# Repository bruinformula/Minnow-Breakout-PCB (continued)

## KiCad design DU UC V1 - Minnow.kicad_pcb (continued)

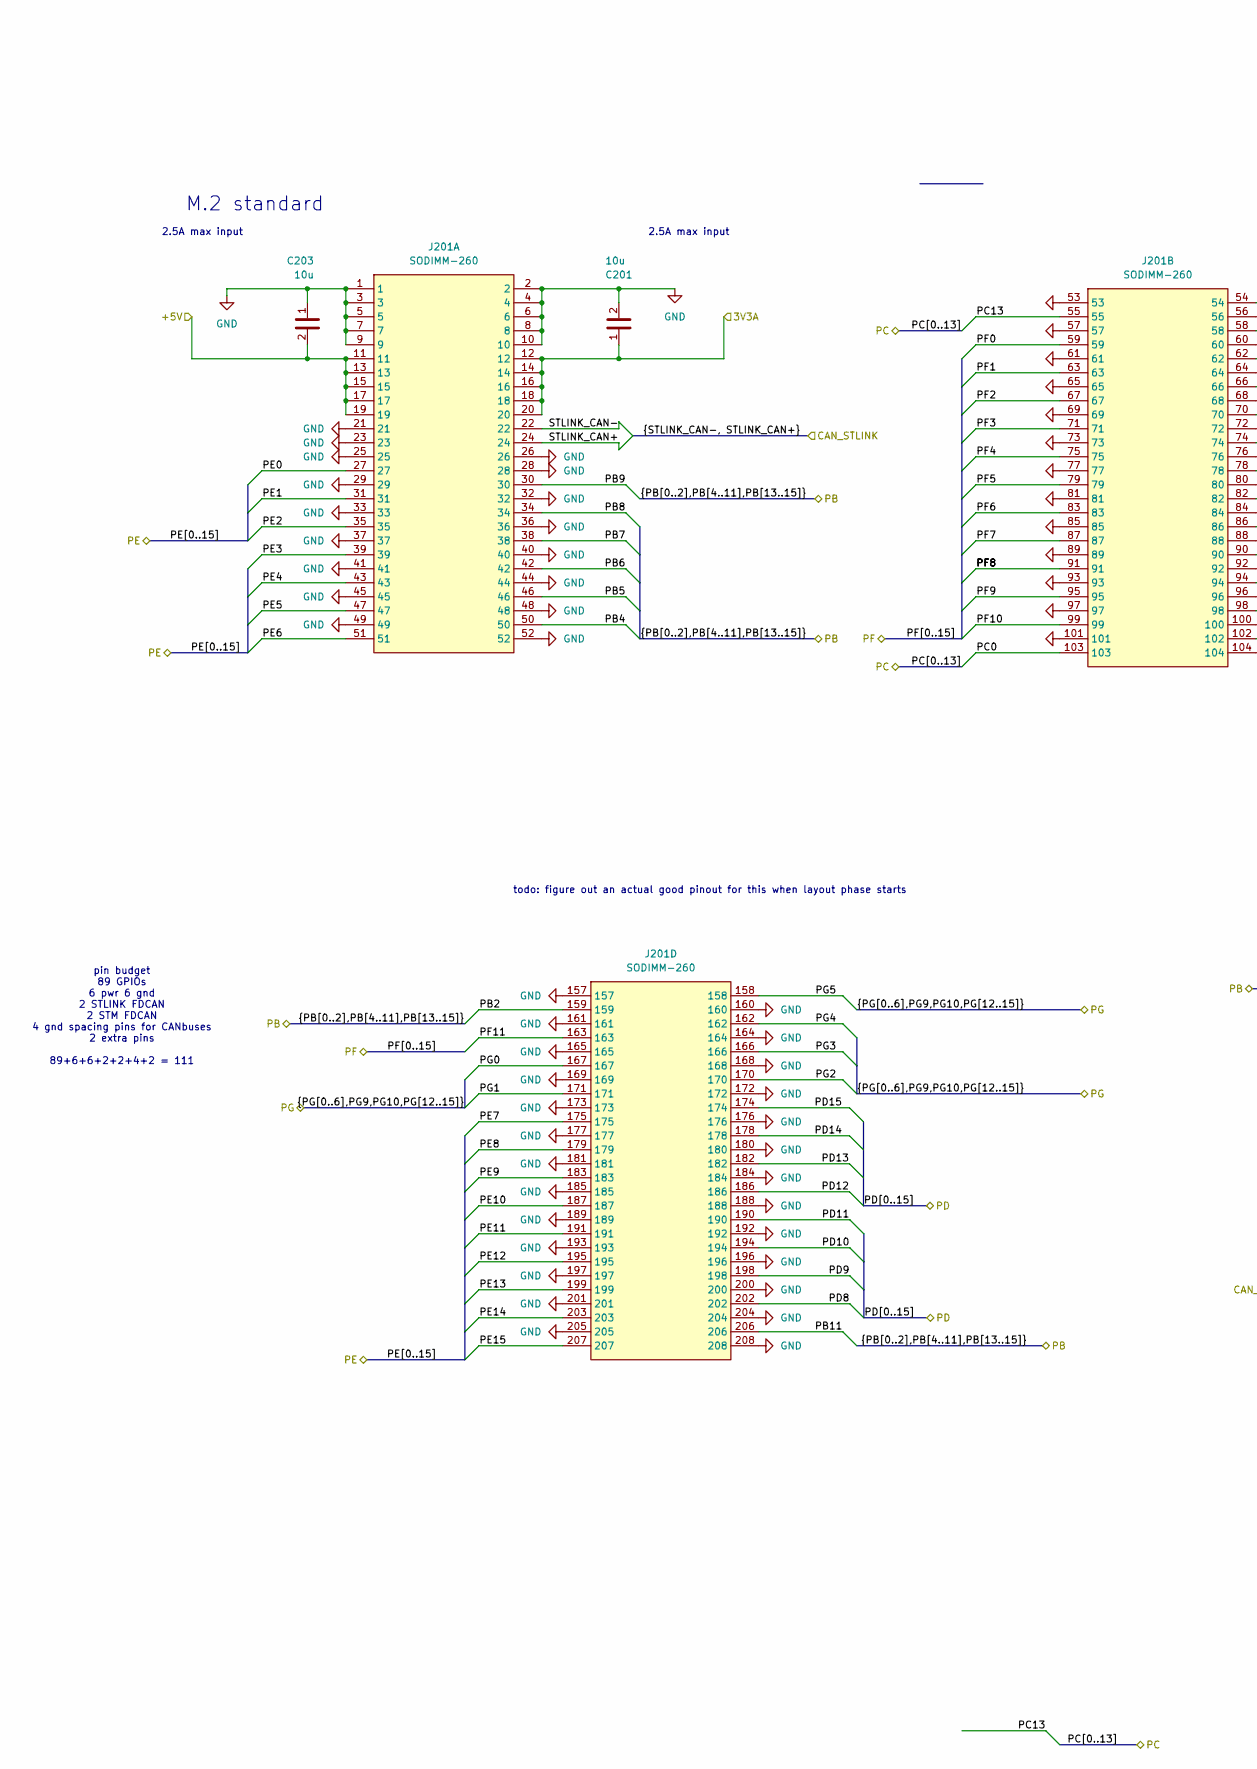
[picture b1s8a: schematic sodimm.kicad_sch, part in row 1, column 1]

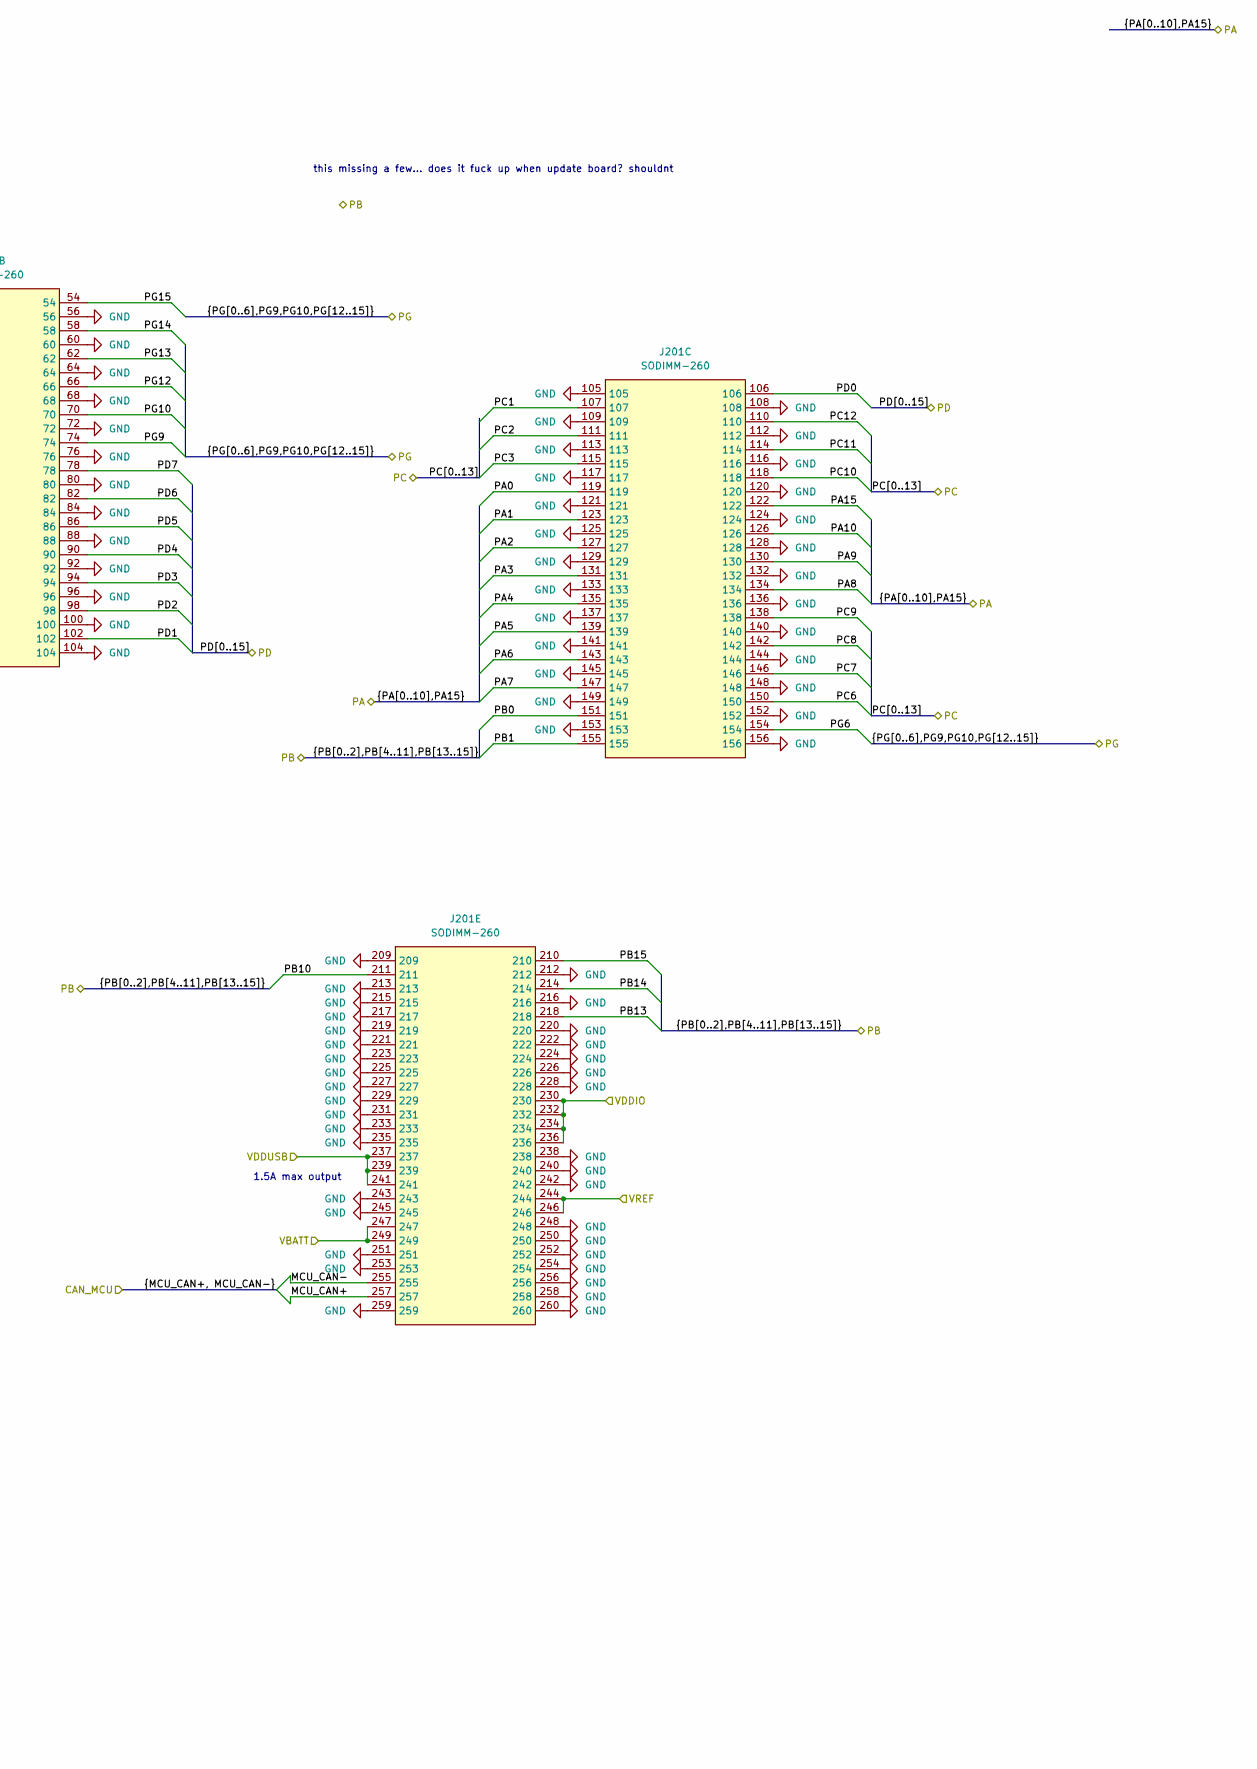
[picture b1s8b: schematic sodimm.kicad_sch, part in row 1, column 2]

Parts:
C201, C203: 10u; C_0603_1608Metric_Pad1.08x0.95mm_HandSolder; Mouser P/N 81-GRM188R61E106MA3D
J201: SODIMM-260; SODIMM-260 DDR4; Manufacturer P/N 2309407-1; Digikey P/N A126758TR-ND

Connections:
/3V3A_RAW: C201.1, J201.12, J201.14, J201.16, J201.18, J201.20; also elsewhere on the board
/5V_RAW: C203.2, J201.11, J201.13, J201.15, J201.17, J201.19; also elsewhere on the board
/SODIMM Connector/MCU_CAN+: J201.257; also elsewhere on the board
/SODIMM Connector/MCU_CAN-: J201.255; also elsewhere on the board
/SODIMM Connector/PA0: J201.119; also elsewhere on the board
/SODIMM Connector/PA1: J201.123; also elsewhere on the board
/SODIMM Connector/PA2: J201.127; also elsewhere on the board
/SODIMM Connector/PA3: J201.131; also elsewhere on the board
/SODIMM Connector/PA4: J201.135; also elsewhere on the board
/SODIMM Connector/PA5: J201.139; also elsewhere on the board
/SODIMM Connector/PA6: J201.143; also elsewhere on the board
/SODIMM Connector/PA7: J201.147; also elsewhere on the board
/SODIMM Connector/PA8: J201.134; also elsewhere on the board
/SODIMM Connector/PA9: J201.130; also elsewhere on the board
/SODIMM Connector/PA10: J201.126; also elsewhere on the board
/SODIMM Connector/PA15: J201.122; also elsewhere on the board
/SODIMM Connector/PB0: J201.151; also elsewhere on the board
/SODIMM Connector/PB1: J201.155; also elsewhere on the board
/SODIMM Connector/PB2: J201.159; also elsewhere on the board
/SODIMM Connector/PB4: J201.50; also elsewhere on the board
/SODIMM Connector/PB5: J201.46; also elsewhere on the board
/SODIMM Connector/PB6: J201.42; also elsewhere on the board
/SODIMM Connector/PB7: J201.38; also elsewhere on the board
/SODIMM Connector/PB8: J201.34; also elsewhere on the board
/SODIMM Connector/PB9: J201.30; also elsewhere on the board
/SODIMM Connector/PB10: J201.211; also elsewhere on the board
/SODIMM Connector/PB11: J201.206; also elsewhere on the board
/SODIMM Connector/PB13: J201.218; also elsewhere on the board
/SODIMM Connector/PB14: J201.214; also elsewhere on the board
/SODIMM Connector/PB15: J201.210; also elsewhere on the board
/SODIMM Connector/PC0: J201.103; also elsewhere on the board
/SODIMM Connector/PC1: J201.107; also elsewhere on the board
/SODIMM Connector/PC2: J201.111; also elsewhere on the board
/SODIMM Connector/PC3: J201.115; also elsewhere on the board
/SODIMM Connector/PC6: J201.150; also elsewhere on the board
/SODIMM Connector/PC7: J201.146; also elsewhere on the board
/SODIMM Connector/PC8: J201.142; also elsewhere on the board
/SODIMM Connector/PC9: J201.138; also elsewhere on the board
/SODIMM Connector/PC10: J201.118; also elsewhere on the board
/SODIMM Connector/PC11: J201.114; also elsewhere on the board
/SODIMM Connector/PC12: J201.110; also elsewhere on the board
/SODIMM Connector/PC13: J201.55; also elsewhere on the board
/SODIMM Connector/PD0: J201.106; also elsewhere on the board
/SODIMM Connector/PD1: J201.102; also elsewhere on the board
/SODIMM Connector/PD2: J201.98; also elsewhere on the board
/SODIMM Connector/PD3: J201.94; also elsewhere on the board
/SODIMM Connector/PD4: J201.90; also elsewhere on the board
/SODIMM Connector/PD5: J201.86; also elsewhere on the board
/SODIMM Connector/PD6: J201.82; also elsewhere on the board
/SODIMM Connector/PD7: J201.78; also elsewhere on the board
/SODIMM Connector/PD8: J201.202; also elsewhere on the board
/SODIMM Connector/PD9: J201.198; also elsewhere on the board
/SODIMM Connector/PD10: J201.194; also elsewhere on the board
/SODIMM Connector/PD11: J201.190; also elsewhere on the board
/SODIMM Connector/PD12: J201.186; also elsewhere on the board
/SODIMM Connector/PD13: J201.182; also elsewhere on the board
/SODIMM Connector/PD14: J201.178; also elsewhere on the board
/SODIMM Connector/PD15: J201.174; also elsewhere on the board
/SODIMM Connector/PE0: J201.27; also elsewhere on the board
/SODIMM Connector/PE1: J201.31; also elsewhere on the board
/SODIMM Connector/PE2: J201.35; also elsewhere on the board
/SODIMM Connector/PE3: J201.39; also elsewhere on the board
/SODIMM Connector/PE4: J201.43; also elsewhere on the board
/SODIMM Connector/PE5: J201.47; also elsewhere on the board
/SODIMM Connector/PE6: J201.51; also elsewhere on the board
/SODIMM Connector/PE7: J201.175; also elsewhere on the board
/SODIMM Connector/PE8: J201.179; also elsewhere on the board
/SODIMM Connector/PE9: J201.183; also elsewhere on the board
/SODIMM Connector/PE10: J201.187; also elsewhere on the board
/SODIMM Connector/PE11: J201.191; also elsewhere on the board
/SODIMM Connector/PE12: J201.195; also elsewhere on the board
/SODIMM Connector/PE13: J201.199; also elsewhere on the board
/SODIMM Connector/PE14: J201.203; also elsewhere on the board
/SODIMM Connector/PE15: J201.207; also elsewhere on the board
/SODIMM Connector/PF0: J201.59; also elsewhere on the board
/SODIMM Connector/PF1: J201.63; also elsewhere on the board
/SODIMM Connector/PF2: J201.67; also elsewhere on the board
/SODIMM Connector/PF3: J201.71; also elsewhere on the board
/SODIMM Connector/PF4: J201.75; also elsewhere on the board
/SODIMM Connector/PF5: J201.79; also elsewhere on the board
/SODIMM Connector/PF6: J201.83; also elsewhere on the board
/SODIMM Connector/PF7: J201.87; also elsewhere on the board
/SODIMM Connector/PF8: J201.91; also elsewhere on the board
/SODIMM Connector/PF9: J201.95; also elsewhere on the board
/SODIMM Connector/PF10: J201.99; also elsewhere on the board
/SODIMM Connector/PF11: J201.163; also elsewhere on the board
/SODIMM Connector/PG0: J201.167; also elsewhere on the board
/SODIMM Connector/PG1: J201.171; also elsewhere on the board
/SODIMM Connector/PG2: J201.170; also elsewhere on the board
/SODIMM Connector/PG3: J201.166; also elsewhere on the board
/SODIMM Connector/PG4: J201.162; also elsewhere on the board
/SODIMM Connector/PG5: J201.158; also elsewhere on the board
/SODIMM Connector/PG6: J201.154; also elsewhere on the board
/SODIMM Connector/PG9: J201.74; also elsewhere on the board
/SODIMM Connector/PG10: J201.70; also elsewhere on the board
/SODIMM Connector/PG12: J201.66; also elsewhere on the board
/SODIMM Connector/PG13: J201.62; also elsewhere on the board
/SODIMM Connector/PG14: J201.58; also elsewhere on the board
/SODIMM Connector/PG15: J201.54; also elsewhere on the board
/SODIMM Connector/VBATT: J201.247, J201.249; also elsewhere on the board
/SODIMM Connector/VDDIO: J201.230, J201.232, J201.234, J201.236; also elsewhere on the board
/SODIMM Connector/VDDUSB: J201.237, J201.239, J201.241; also elsewhere on the board
/SODIMM Connector/VREF: J201.244, J201.246; also elsewhere on the board
/STLINK_CAN+: J201.24; also elsewhere on the board
/STLINK_CAN-: J201.22; also elsewhere on the board
GND: C201.2, C203.1, J201.1, J201.2, J201.3, J201.4, J201.5, J201.6, J201.7, J201.8, J201.9, J201.10, J201.21, J201.23, J201.25, J201.26, J201.28, J201.29, J201.32, J201.33, J201.36, J201.37, J201.40, J201.41, J201.44, J201.45, J201.48, J201.49, J201.52, J201.53, J201.56, J201.57, J201.60, J201.61, J201.64, J201.65, J201.68, J201.69, J201.72, J201.73, J201.76, J201.77, J201.80, J201.81, J201.84, J201.85, J201.88, J201.89, J201.92, J201.93, J201.96, J201.97, J201.100, J201.101, J201.104, J201.105, J201.108, J201.109, J201.112, J201.113, J201.116, J201.117, J201.120, J201.121, J201.124, J201.125, J201.128, J201.129, J201.132, J201.133, J201.136, J201.137, J201.140, J201.141, J201.144, J201.145, J201.148, J201.149, J201.152, J201.153, J201.156, J201.157, J201.160, J201.161, J201.164, J201.165, J201.168, J201.169, J201.172, J201.173, J201.176, J201.177, J201.180, J201.181, J201.184, J201.185, J201.188, J201.189, J201.192, J201.193, J201.196, J201.197, J201.200, J201.201, J201.204, J201.205, J201.208, J201.209, J201.212, J201.213, J201.215, J201.216, J201.217, J201.219, J201.220, J201.221, J201.222, J201.223, J201.224, J201.225, J201.226, J201.227, J201.228, J201.229, J201.231, J201.233, J201.235, J201.238, J201.240, J201.242, J201.243, J201.245, J201.248, J201.250, J201.251, J201.252, J201.253, J201.254, J201.256, J201.258, J201.259, J201.260; also elsewhere on the board

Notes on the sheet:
pin budget 89 GPIOs 6 pwr 6 gnd 2 STLINK FDCAN 2 STM FDCAN 4 gnd spacing pins for CANbuses 2 extra pins 89+6+6+2+2+4+2 = 111
1.5A max output
2.5A max input
todo: figure out an actual good pinout for this when layout phase starts
this missing a few... does it fuck up when update board? shouldnt
M.2 standard

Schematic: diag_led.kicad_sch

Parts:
D1301: Green; D_0805_2012Metric_Pad1.15x1.40mm_HandSolder; Mouser P/N 755-SMLMN2ECTT86C; Digikey P/N 846-SMLMN2ECTT86CCT-ND
Q1301: BSS84; SOT-23
R1301: 120; R_0603_1608Metric_Pad0.98x0.95mm_HandSolder; Mouser P/N 708-RMCF0603FT120R; Digikey P/N RMCF0603FT120RCT-ND

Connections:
+3.3V: Q1301.2 (S); also elsewhere on the board
/Power/Diagnostic LED/SIG: Q1301.1 (G); also elsewhere on the board
GND: D1301.1 (K); also elsewhere on the board
unnamed: D1301.2 (A), R1301.1
unnamed: Q1301.3 (D), R1301.2

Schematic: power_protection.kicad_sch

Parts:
D1401, D1402: 20V; D_SMB; Manufacturer P/N 1SMB5913BT3; Digikey P/N 1SMB5932BT3GOSCT-ND
R1401: 470; R_0402_1005Metric_Pad0.72x0.64mm_HandSolder; Mouser P/N 708-RMCF0402FT470R; Digikey P/N RMCF0402FT470RCT-ND
R1402, R1405: 360; R_0603_1608Metric_Pad0.98x0.95mm_HandSolder; Mouser P/N 708-RMCF0603FT360R; Digikey P/N RMCF0603FT360RCT-ND
R1403, R1406: 390; R_0603_1608Metric_Pad0.98x0.95mm_HandSolder; Mouser P/N 708-RMCF0603FT390R; Digikey P/N RMCF0603FT390RCT-ND
R1404: 270; R_0603_1608Metric_Pad0.98x0.95mm_HandSolder; Mouser P/N 708-RMCF0603FT270R; Digikey P/N RMCF0603FT270RCT-ND
R1407, R1408: 100k; R_0402_1005Metric_Pad0.72x0.64mm_HandSolder; Mouser P/N 708-RMCF0402FT100K; Digikey P/N RMCF0402FT100KCT-ND
U1401, U1402: TPS25961; WSON-6-1EP_2x2mm_P0.65mm_EP1x1.6mm; Mouser P/N 595-TPS25961DRVR; Digikey P/N 296-TPS25961DRVRCT-ND

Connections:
/3V3A_RAW: D1401.1 (K), R1404.2, U1402.6 (VIN); also elsewhere on the board
/5V_RAW: D1402.1 (K), R1401.2, U1401.6 (VIN); also elsewhere on the board
/Power/Power Protection/3V3A_PROT: U1402.1 (VOUT); also elsewhere on the board
/Power/Power Protection/5V_PROT: U1401.1 (VOUT); also elsewhere on the board
GND: D1401.2 (A), D1402.2 (A), R1403.1, R1406.1, R1407.1, R1408.1, U1401.4 (GND), U1401.7 (EP), U1402.4 (GND), U1402.7 (EP); also elsewhere on the board
unnamed: R1401.1, R1402.2, U1401.5 (EN/UVLO)
unnamed: R1407.2, U1401.3 (ILIM)
unnamed: R1402.1, R1403.2, U1401.2 (OVLO)
unnamed: R1404.1, R1405.2, U1402.5 (EN/UVLO)
unnamed: R1408.2, U1402.3 (ILIM)
unnamed: R1405.1, R1406.2, U1402.2 (OVLO)

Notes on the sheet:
maybe add tvs
can carry up to 3.9A without exploding; 150C max temp, 30C ambient, 125C/W thermal res., 50mOhm RdsON, 1.25FOS; ((150-30)/1.25 * 1/125)/0.05 = 15.36A^2 => 3.919, so 3.9A

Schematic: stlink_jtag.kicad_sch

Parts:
J1801: Conn_02x05_Odd_Even; PinHeader_2x05_P2.54mm_Vertical_SMD
JP1801, JP1802, JP1803, JP1804: SolderJumper_2_Bridged; SolderJumper-2_P1.3mm_Bridged_Pad1.0x1.5mm
JP1805, JP1806, JP1807, JP1808: SolderJumper_2_Open; SolderJumper-2_P1.3mm_Open_Pad1.0x1.5mm
R1801: 10k; R_0402_1005Metric_Pad0.72x0.64mm_HandSolder; Mouser P/N 708-RMCF0402FT10K0; Digikey P/N RMCF0402FT10K0CT-ND
R1802, R1803, R1804, R1805: 22; R_0402_1005Metric_Pad0.72x0.64mm_HandSolder; Mouser P/N 708-RMCF0402FT22R0; Digikey P/N RMCF0402FT22R0CT-ND

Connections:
/5V_RAW: J1801.1, R1801.2; also elsewhere on the board
/ST-link V2/3V3_STLINK: JP1805.2 (B)
/ST-link V2/MCU_NRST: J1801.7, JP1803.2 (B), JP1807.1 (A); also elsewhere on the board
/ST-link V2/MCU_SWO: J1801.9, JP1804.2 (B), JP1808.1 (A); also elsewhere on the board
/ST-link V2/MCU_TCK: J1801.3, JP1801.2 (B), JP1805.1 (A); also elsewhere on the board
/ST-link V2/MCU_TMS: J1801.5, JP1802.2 (B), JP1806.1 (A); also elsewhere on the board
/ST-link V2/STLINK_DEBUG_JTCK: JP1806.2 (B); also elsewhere on the board
/ST-link V2/STLINK_DEBUG_JTMS: JP1808.2 (B); also elsewhere on the board
/ST-link V2/STLINK_WRITE.JTCK: JP1801.1 (A), R1802.2; also elsewhere on the board
/ST-link V2/STLINK_WRITE.JTMS: JP1802.1 (A), R1803.2; also elsewhere on the board
/ST-link V2/STLINK_WRITE.SWO: JP1804.1 (A), R1805.2; also elsewhere on the board
/ST-link V2/STLINK_WRITE.nRST: JP1803.1 (A), R1804.2; also elsewhere on the board
GND: J1801.2, JP1807.2 (B), R1801.1; also elsewhere on the board
unnamed: J1801.4, R1802.1
unnamed: J1801.6, R1803.1
unnamed: J1801.8, R1804.1
unnamed: J1801.10, R1805.1

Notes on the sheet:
lmao r these harwin bullshits strong enough to endure formula nerds playing w it
PROBABLY: connect J4 to STLINK JTAG
some diode and resistor here that idk what is going on w
"DEFAULT" no idea wtf that means datasheet says not to modify
do i even need this shit
PROBABLY: connect STLINK JTAG to MCU JTAG
"RESERVED" no idea wtf that means datasheet says not to modify
SWD
when these r connected 6pin J3 also is connected to stlink-MCU write bus

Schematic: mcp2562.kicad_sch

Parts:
C701: 100n; C_0603_1608Metric_Pad1.08x0.95mm_HandSolder; Mouser P/N 603-CC603KRX7R9BB104; Digikey P/N 1276-CL05B104KB54PNCCT-ND
D701, D702: White; D_0603_1608Metric_Pad1.05x0.95mm_HandSolder; Mouser P/N 743-IN-S63AT5UW; Digikey P/N 1830-1063-1-ND
JP701: CAN_TERM; SolderJumper-2_P1.3mm_Open_RoundedPad1.0x1.5mm
Q701, Q702: BSS84; SOT-23
R701: 120; R_0402_1005Metric_Pad0.72x0.64mm_HandSolder; Mouser P/N 708-RMCF0402FT120R; Digikey P/N RMCF0402FT120RCT-ND
R702, R703: 120; R_0603_1608Metric_Pad0.98x0.95mm_HandSolder; Mouser P/N 708-RMCF0603FT120R; Digikey P/N RMCF0603FT120RCT-ND
U701: TCAN334G; TSOT-23-8

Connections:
+3.3V: C701.1, Q701.2 (S), Q702.2 (S), U701.3 (VCC); also elsewhere on the board
/SODIMM Connector/MCU_CAN+: JP701.1 (A), U701.7 (CANH); also elsewhere on the board
/SODIMM Connector/MCU_CAN-: R701.1, U701.6 (CANL); also elsewhere on the board
/STM32L552ZET6Q/CAN2_RX: Q702.1 (G), U701.4 (RXD); also elsewhere on the board
/STM32L552ZET6Q/CAN2_TX: Q701.1 (G), U701.1 (TXD); also elsewhere on the board
GND: C701.2, D701.1 (K), D702.1 (K), U701.2 (GND), U701.5 (SHDN), U701.8 (STB); also elsewhere on the board
unnamed: D701.2 (A), R702.1
unnamed: D702.2 (A), R703.1
unnamed: JP701.2 (B), R701.2
unnamed: Q701.3 (D), R702.2
unnamed: Q702.3 (D), R703.2

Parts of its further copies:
C1501: 100n; C_0603_1608Metric_Pad1.08x0.95mm_HandSolder; Mouser P/N 603-CC603KRX7R9BB104; Digikey P/N 1276-CL05B104KB54PNCCT-ND
D1501, D1502: White; D_0603_1608Metric_Pad1.05x0.95mm_HandSolder; Mouser P/N 743-IN-S63AT5UW; Digikey P/N 1830-1063-1-ND
JP1501: CAN_TERM; SolderJumper-2_P1.3mm_Open_RoundedPad1.0x1.5mm
Q1501, Q1502: BSS84; SOT-23
R1501: 120; R_0402_1005Metric_Pad0.72x0.64mm_HandSolder; Mouser P/N 708-RMCF0402FT120R; Digikey P/N RMCF0402FT120RCT-ND
R1502, R1503: 120; R_0603_1608Metric_Pad0.98x0.95mm_HandSolder; Mouser P/N 708-RMCF0603FT120R; Digikey P/N RMCF0603FT120RCT-ND
U1501: TCAN334G; TSOT-23-8

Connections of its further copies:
+3.3V: C1501.1, Q1501.2 (S), Q1502.2 (S), U1501.3 (VCC); also elsewhere on the board
/ST-link V2/CAN_RX: Q1502.1 (G), U1501.4 (RXD); also elsewhere on the board
/ST-link V2/CAN_TX: Q1501.1 (G), U1501.1 (TXD); also elsewhere on the board
/STLINK_CAN+: JP1501.1 (A), U1501.7 (CANH); also elsewhere on the board
/STLINK_CAN-: R1501.1, U1501.6 (CANL); also elsewhere on the board
GND: C1501.2, D1501.1 (K), D1502.1 (K), U1501.2 (GND), U1501.5 (SHDN), U1501.8 (STB); also elsewhere on the board
unnamed: D1501.2 (A), R1502.1
unnamed: D1502.2 (A), R1503.1
unnamed: JP1501.2 (B), R1501.2
unnamed: Q1501.3 (D), R1502.2
unnamed: Q1502.3 (D), R1503.2

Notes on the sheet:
TX LED
RX LED
Connect 2&3 to use terminating resistor

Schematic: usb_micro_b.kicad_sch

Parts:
D1701: 600m; D_SOD-323_HandSoldering; Mouser P/N 833-B5819WS-TP; LCSC P/N C191023
J1701: MicroUSB; USB_Micro-B_Molex-105133-0001; Mouser P/N 538-105133-0001; Digikey P/N WM9734CT-ND
Q1701: MMBT3904; SOT-23
R1701: 10k; R_0402_1005Metric_Pad0.72x0.64mm_HandSolder; Mouser P/N 708-RMCF0402FT10K0; Digikey P/N RMCF0402FT10K0CT-ND
R1702: 36k; R_0603_1608Metric_Pad0.98x0.95mm_HandSolder; Mouser P/N 708-RMCF0603FT36K0; Digikey P/N RMCF0603FT36K0CT-ND
R1703: 1.5k; R_0402_1005Metric_Pad0.72x0.64mm_HandSolder; Mouser P/N 708-RMCF0402FT1K50; Digikey P/N RMCF0402FT1K50CT-ND
R1704: 100k; R_0402_1005Metric_Pad0.72x0.64mm_HandSolder; Mouser P/N 708-RMCF0402FT100K; Digikey P/N RMCF0402FT100KCT-ND
U1701: PSM712-LF-T7; SOT-23; Manufacturer P/N PSM712-LF-T7; Digikey P/N 4518-PSM712-LF-T7CT-ND

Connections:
+3.3V: Q1701.3 (C); also elsewhere on the board
/5V_RAW: D1701.1 (K), R1701.2; also elsewhere on the board
/ST-link V2/USB Micro-B/PP5000_VUSB_RAW: D1701.2 (A), J1701.1 (VBUS)
/ST-link V2/USB Micro-B/USB_ID: J1701.4 (ID), R1704.2
/ST-link V2/USB_D+: J1701.3 (D+), U1701.1; also elsewhere on the board
/ST-link V2/USB_D-: J1701.2 (D-), R1703.1, U1701.2; also elsewhere on the board
/ST-link V2/USB_RENUMn: Q1701.1 (B), R1701.1, R1702.2; also elsewhere on the board
GND: J1701.5 (GND), J1701.6 (Shield), R1702.1, R1704.1, U1701.3; also elsewhere on the board
unnamed: Q1701.2 (E), R1703.2

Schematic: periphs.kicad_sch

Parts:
U501: STM32L552ZET6Q; LQFP-144_20x20mm_P0.5mm; Manufacturer P/N STM32L552ZET6Q; LCSC P/N TO ORDER

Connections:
/Debug LED Array/A0: U501.50 (PF13); also elsewhere on the board
/Debug LED Array/A1: U501.51 (PF14); also elsewhere on the board
/Debug LED Array/A2: U501.52 (PF15); also elsewhere on the board
/Debug LED Array/EN: U501.47 (PF12); also elsewhere on the board
/SODIMM Connector/PA0: U501.33 (PA0); also elsewhere on the board
/SODIMM Connector/PA1: U501.34 (PA1); also elsewhere on the board
/SODIMM Connector/PA2: U501.35 (PA2); also elsewhere on the board
/SODIMM Connector/PA3: U501.36 (PA3); also elsewhere on the board
/SODIMM Connector/PA4: U501.39 (PA4); also elsewhere on the board
/SODIMM Connector/PA5: U501.40 (PA5); also elsewhere on the board
/SODIMM Connector/PA6: U501.41 (PA6); also elsewhere on the board
/SODIMM Connector/PA7: U501.42 (PA7); also elsewhere on the board
/SODIMM Connector/PA8: U501.100 (PA8); also elsewhere on the board
/SODIMM Connector/PA9: U501.101 (PA9); also elsewhere on the board
/SODIMM Connector/PA10: U501.102 (PA10); also elsewhere on the board
/SODIMM Connector/PB0: U501.43 (PB0); also elsewhere on the board
/SODIMM Connector/PB1: U501.44 (PB1); also elsewhere on the board
/SODIMM Connector/PB2: U501.45 (PB2); also elsewhere on the board
/SODIMM Connector/PB4: U501.133 (PB4); also elsewhere on the board
/SODIMM Connector/PB5: U501.134 (PB5); also elsewhere on the board
/SODIMM Connector/PB6: U501.135 (PB6); also elsewhere on the board
/SODIMM Connector/PB7: U501.136 (PB7); also elsewhere on the board
/SODIMM Connector/PB8: U501.138 (PB8); also elsewhere on the board
/SODIMM Connector/PB9: U501.139 (PB9); also elsewhere on the board
/SODIMM Connector/PB10: U501.66 (PB10); also elsewhere on the board
/SODIMM Connector/PB11: U501.67 (PB11); also elsewhere on the board
/SODIMM Connector/PB13: U501.74 (PB13); also elsewhere on the board
/SODIMM Connector/PB14: U501.75 (PB14); also elsewhere on the board
/SODIMM Connector/PB15: U501.76 (PB15); also elsewhere on the board
/SODIMM Connector/PC0: U501.26 (PC0); also elsewhere on the board
/SODIMM Connector/PC1: U501.27 (PC1); also elsewhere on the board
/SODIMM Connector/PC2: U501.28 (PC2); also elsewhere on the board
/SODIMM Connector/PC3: U501.29 (PC3); also elsewhere on the board
/SODIMM Connector/PC6: U501.96 (PC6); also elsewhere on the board
/SODIMM Connector/PC7: U501.97 (PC7); also elsewhere on the board
/SODIMM Connector/PC8: U501.98 (PC8); also elsewhere on the board
/SODIMM Connector/PC9: U501.99 (PC9); also elsewhere on the board
/SODIMM Connector/PC13: U501.7 (PC13); also elsewhere on the board
/SODIMM Connector/PD0: U501.114 (PD0); also elsewhere on the board
/SODIMM Connector/PD1: U501.115 (PD1); also elsewhere on the board
/SODIMM Connector/PD2: U501.116 (PD2); also elsewhere on the board
/SODIMM Connector/PD3: U501.117 (PD3); also elsewhere on the board
/SODIMM Connector/PD4: U501.118 (PD4); also elsewhere on the board
/SODIMM Connector/PD5: U501.119 (PD5); also elsewhere on the board
/SODIMM Connector/PD6: U501.122 (PD6); also elsewhere on the board
/SODIMM Connector/PD7: U501.123 (PD7); also elsewhere on the board
/SODIMM Connector/PD8: U501.77 (PD8); also elsewhere on the board
/SODIMM Connector/PD9: U501.78 (PD9); also elsewhere on the board
/SODIMM Connector/PD10: U501.79 (PD10); also elsewhere on the board
/SODIMM Connector/PD11: U501.80 (PD11); also elsewhere on the board
/SODIMM Connector/PD12: U501.81 (PD12); also elsewhere on the board
/SODIMM Connector/PD13: U501.82 (PD13); also elsewhere on the board
/SODIMM Connector/PD14: U501.85 (PD14); also elsewhere on the board
/SODIMM Connector/PD15: U501.86 (PD15); also elsewhere on the board
/SODIMM Connector/PE0: U501.140 (PE0); also elsewhere on the board
/SODIMM Connector/PE1: U501.141 (PE1); also elsewhere on the board
/SODIMM Connector/PE2: U501.1 (PE2); also elsewhere on the board
/SODIMM Connector/PE3: U501.2 (PE3); also elsewhere on the board
/SODIMM Connector/PE4: U501.3 (PE4); also elsewhere on the board
/SODIMM Connector/PE5: U501.4 (PE5); also elsewhere on the board
/SODIMM Connector/PE6: U501.5 (PE6); also elsewhere on the board
/SODIMM Connector/PE7: U501.55 (PE7); also elsewhere on the board
/SODIMM Connector/PE8: U501.56 (PE8); also elsewhere on the board
/SODIMM Connector/PE9: U501.57 (PE9); also elsewhere on the board
/SODIMM Connector/PE10: U501.60 (PE10); also elsewhere on the board
/SODIMM Connector/PE11: U501.61 (PE11); also elsewhere on the board
/SODIMM Connector/PE12: U501.62 (PE12); also elsewhere on the board
/SODIMM Connector/PE13: U501.63 (PE13); also elsewhere on the board
/SODIMM Connector/PE14: U501.64 (PE14); also elsewhere on the board
/SODIMM Connector/PE15: U501.65 (PE15); also elsewhere on the board
/SODIMM Connector/PF0: U501.10 (PF0); also elsewhere on the board
/SODIMM Connector/PF1: U501.11 (PF1); also elsewhere on the board
/SODIMM Connector/PF2: U501.12 (PF2); also elsewhere on the board
/SODIMM Connector/PF3: U501.13 (PF3); also elsewhere on the board
/SODIMM Connector/PF4: U501.14 (PF4); also elsewhere on the board
/SODIMM Connector/PF5: U501.15 (PF5); also elsewhere on the board
/SODIMM Connector/PF6: U501.18 (PF6); also elsewhere on the board
/SODIMM Connector/PF7: U501.19 (PF7); also elsewhere on the board
/SODIMM Connector/PF8: U501.20 (PF8); also elsewhere on the board
/SODIMM Connector/PF9: U501.21 (PF9); also elsewhere on the board
/SODIMM Connector/PF10: U501.22 (PF10); also elsewhere on the board
/SODIMM Connector/PF11: U501.46 (PF11); also elsewhere on the board
/SODIMM Connector/PG0: U501.53 (PG0); also elsewhere on the board
/SODIMM Connector/PG1: U501.54 (PG1); also elsewhere on the board
/SODIMM Connector/PG2: U501.87 (PG2); also elsewhere on the board
/SODIMM Connector/PG3: U501.88 (PG3); also elsewhere on the board
/SODIMM Connector/PG4: U501.89 (PG4); also elsewhere on the board
/SODIMM Connector/PG5: U501.90 (PG5); also elsewhere on the board
/SODIMM Connector/PG6: U501.91 (PG6); also elsewhere on the board
/SODIMM Connector/PG9: U501.124 (PG9); also elsewhere on the board
/SODIMM Connector/PG10: U501.125 (PG10); also elsewhere on the board
/SODIMM Connector/PG12: U501.126 (PG12); also elsewhere on the board
/SODIMM Connector/PG13: U501.127 (PG13); also elsewhere on the board
/SODIMM Connector/PG14: U501.128 (PG14); also elsewhere on the board
/SODIMM Connector/PG15: U501.131 (PG15); also elsewhere on the board
/STM32L552ZET6Q/CAN2_RX: U501.103 (PA11); also elsewhere on the board
/STM32L552ZET6Q/CAN2_TX: U501.104 (PA12); also elsewhere on the board
/STM32L552ZET6Q/Peripherals/PA15_IN: U501.110 (PA15); also elsewhere on the board
/STM32L552ZET6Q/Peripherals/PC_IN10: U501.111 (PC10); also elsewhere on the board
/STM32L552ZET6Q/Peripherals/PC_IN11: U501.112 (PC11); also elsewhere on the board
/STM32L552ZET6Q/Peripherals/PC_IN12: U501.113 (PC12); also elsewhere on the board

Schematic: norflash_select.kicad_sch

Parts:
JP1001: NORFLASH_CLK
JP1002: NORFLASH_MISO
JP1003: NORFLASH_MOSI
JP1004: NORFLASH_NSS

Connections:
/NOR Flash/CLK: JP1001.3 (B); also elsewhere on the board
/NOR Flash/CS: JP1004.3 (B); also elsewhere on the board
/NOR Flash/MISO: JP1002.3 (B); also elsewhere on the board
/NOR Flash/MOSI: JP1003.3 (B); also elsewhere on the board
/SODIMM Connector/PA15: JP1004.2 (C); also elsewhere on the board
/SODIMM Connector/PC10: JP1001.2 (C); also elsewhere on the board
/SODIMM Connector/PC11: JP1002.2 (C); also elsewhere on the board
/SODIMM Connector/PC12: JP1003.2 (C); also elsewhere on the board
/STM32L552ZET6Q/Peripherals/PA15_IN: JP1004.1 (A); also elsewhere on the board
/STM32L552ZET6Q/Peripherals/PC_IN10: JP1001.1 (A); also elsewhere on the board
/STM32L552ZET6Q/Peripherals/PC_IN11: JP1002.1 (A); also elsewhere on the board
/STM32L552ZET6Q/Peripherals/PC_IN12: JP1003.1 (A); also elsewhere on the board

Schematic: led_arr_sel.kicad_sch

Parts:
JP1201: LEDARR_EN; SolderJumper-3_P1.3mm_Bridged2Bar12_Pad1.0x1.5mm_NumberLabe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
JP1202: LEDARR_A0; SolderJumper-3_P1.3mm_Bridged2Bar12_Pad1.0x1.5mm_NumberLabe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
JP1203: LEDARR_A1; SolderJumper-3_P1.3mm_Bridged2Bar12_Pad1.0x1.5mm_NumberLabe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
JP1204: LEDARR_A2; SolderJumper-3_P1.3mm_Bridged2Bar12_Pad1.0x1.5mm_NumberLabe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

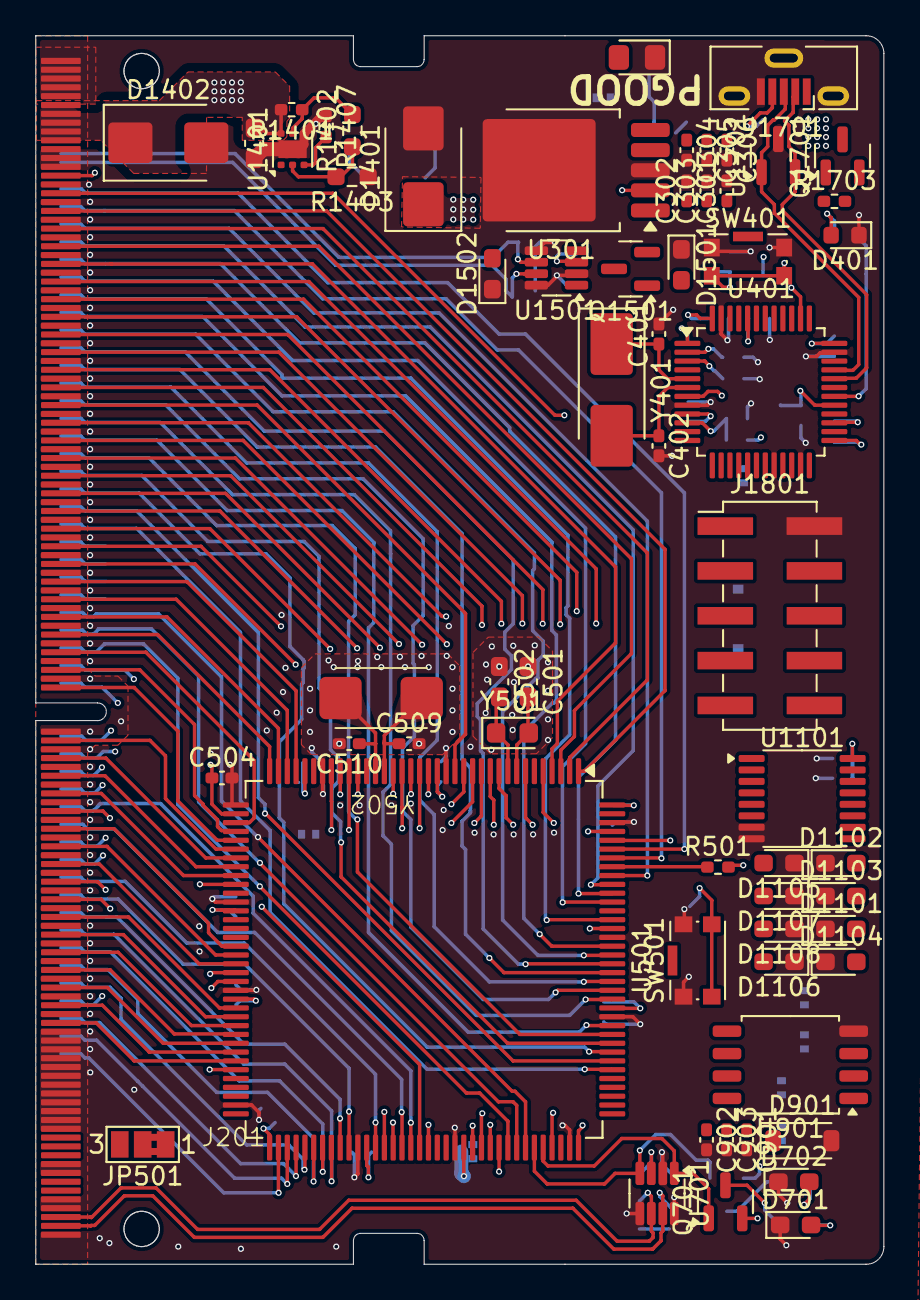
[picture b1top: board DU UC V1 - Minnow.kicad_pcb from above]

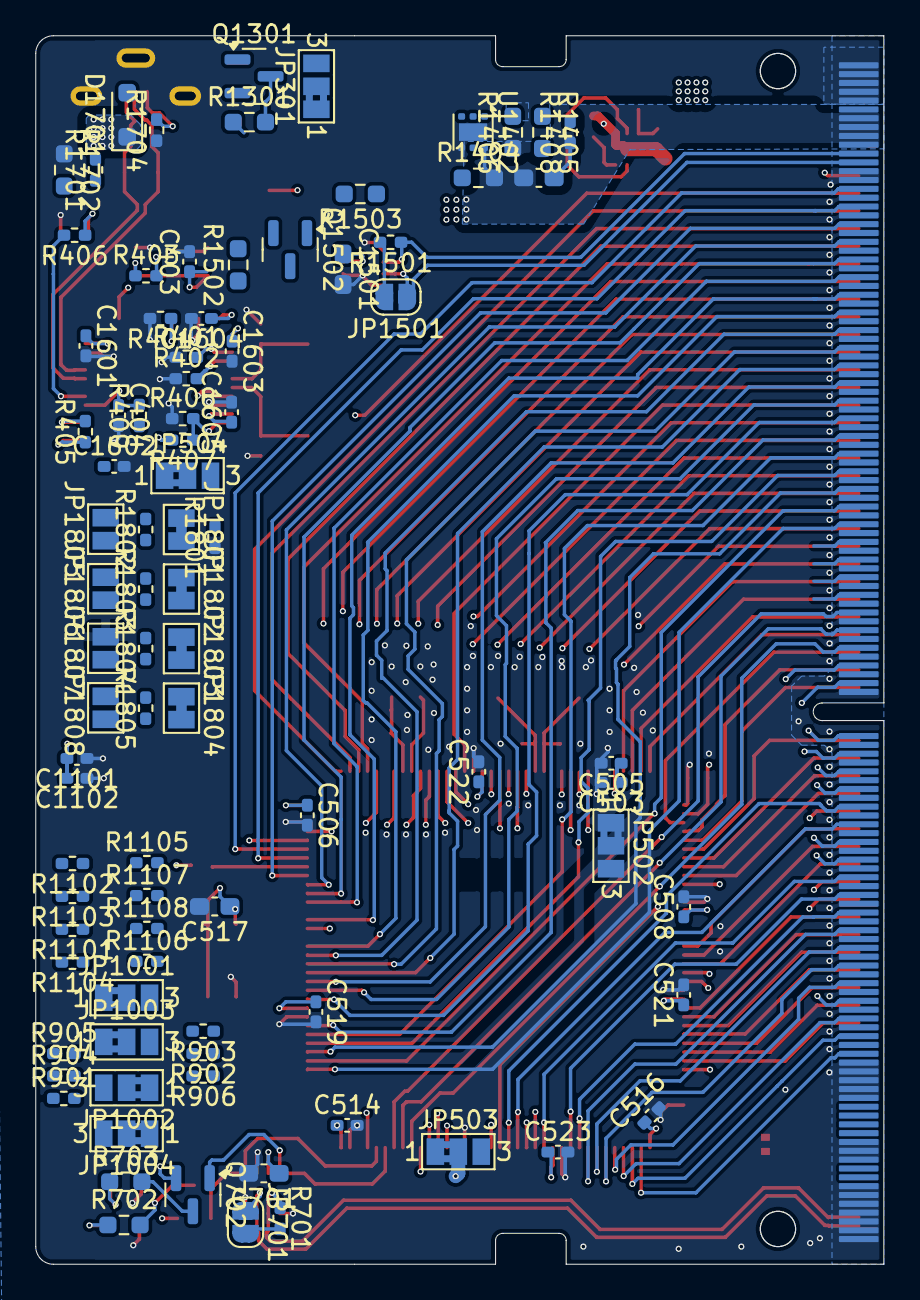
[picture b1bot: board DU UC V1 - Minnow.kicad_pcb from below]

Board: 6 copper layers, 48.0 x 69.6 mm, 149 parts (88 on the bottom side), 205 nets.

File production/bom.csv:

Designator,Footprint,Quantity,Value,LCSC Part #
"C1101, C1102, C1601, C1602, C1603, C1604, C1605, C403, C503, C504, C505, C506, C508, C514, C516, C519, C521, C522, C523, C901, C902, C903",0402,22,100n,C307331
"C1501, C517, C701",0603,3,100n,C14663
"C201, C203",0603,2,10u,C96446
"C301, C302, C303, C304, C305, C306",0402,6,1u,C52923
"C401, C402",0402,2,18p,C1549
C404,0402,1,20p,C1554
"C501, C502",0603,2,7.0p,C1682
"C509, C510",0402,2,22p,C1555
"D1101, D1102, D1103, D1104, D1105, D1106, D1107, D1108",0603,8,Red,C2286
D1301,0805,1,Green,C2297
"D1401, D1402",D_SMB,2,20V,C49452366
"D1501, D1502, D701, D702",0603,4,White,C2290
D1701,D_SOD-323_HandSoldering,1,600m,C191023
D401,0603,1,STLINK,C2286
D901,D_SOD-123,1,3V3,C2112
J1701,USB_Micro-B_Molex-105133-0001,1,MicroUSB,C782257
J1801,PinHeader_2x05_P2.54mm_Vertical_SMD,1,Conn_02x05_Odd_Even,
J201,SODIMM-260 DDR4,1,SODIMM-260,C592559
"Q1301, Q1501, Q1502, Q701, Q702",SOT-23,5,BSS84,
Q1701,SOT-23,1,MMBT3904,
"R1101, R1102, R1103, R1104, R1105, R1106, R1107, R1108",0402,8,220,C25091
"R1301, R1502, R1503, R702, R703",0603,5,120,C22787
R1401,0402,1,470,C25117
"R1402, R1405",0603,2,360,C25194
"R1403, R1406",0603,2,390,C23151
R1404,0603,1,270,C22966
"R1407, R1408, R1704, R403, R404",0402,5,100k,C25741
"R1501, R701",0402,2,120,C25079
"R1701, R1801, R401, R402, R501",0402,5,10k,C25744
R1702,0603,1,36k,C23147
R1703,0402,1,1.5k,C25867
"R1802, R1803, R1804, R1805",0402,4,22,C25092
R405,0402,1,100,C25900
"R406, R409",0402,2,100,C25076
"R407, R408",0402,2,4.7k,C25900
"R901, R902, R903, R904, R905, R906",0402,6,47k,C25792
SW401,SW_Push_1P1T-SH_NO_CK_KMR2xxG,1,STLINK_RST,
SW501,SW_Push_1P1T-SH_NO_CK_KMR2xxG,1,MCU_RST,
U1101,TSSOP-16_4.4x5mm_P0.65mm,1,74HC4051,
"U1401, U1402",WSON-6-1EP_2x2mm_P0.65mm_EP1x1.6mm,2,TPS25961,C5571272
"U1501, U701",TSOT-23-8,2,TCAN334G,
U1701,SOT-23,1,PSM712-LF-T7,C32677 
U301,TO-252-5_TabPin3,1,TPS7B8733QKVURQ1,C3752877
U401,LQFP-48_7x7mm_P0.5mm,1,STM32F103CBTx,C8304
U501,LQFP-144_20x20mm_P0.5mm,1,STM32L552ZET6Q,TO ORDER
U901,SOIC-8_5.3x5.3mm_P1.27mm,1,MX25R3235FM2xx1,C2802828
Y401,Crystal_SMD_5032-2Pin_5.0x3.2mm_HandSoldering,1,8MHz 5pF,C115962
Y501,Crystal_SMD_2012-2Pin_2.0x1.2mm_HandSoldering,1,"32.768kHz, 1.2pF",C5341286
Y502,ABM3-16.000MHZ-D2Y-T,1,"16MHz, 7pF",C596861
